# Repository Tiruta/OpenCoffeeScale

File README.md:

# OpenCoffeeScale
an open sourced compact coffee scale.

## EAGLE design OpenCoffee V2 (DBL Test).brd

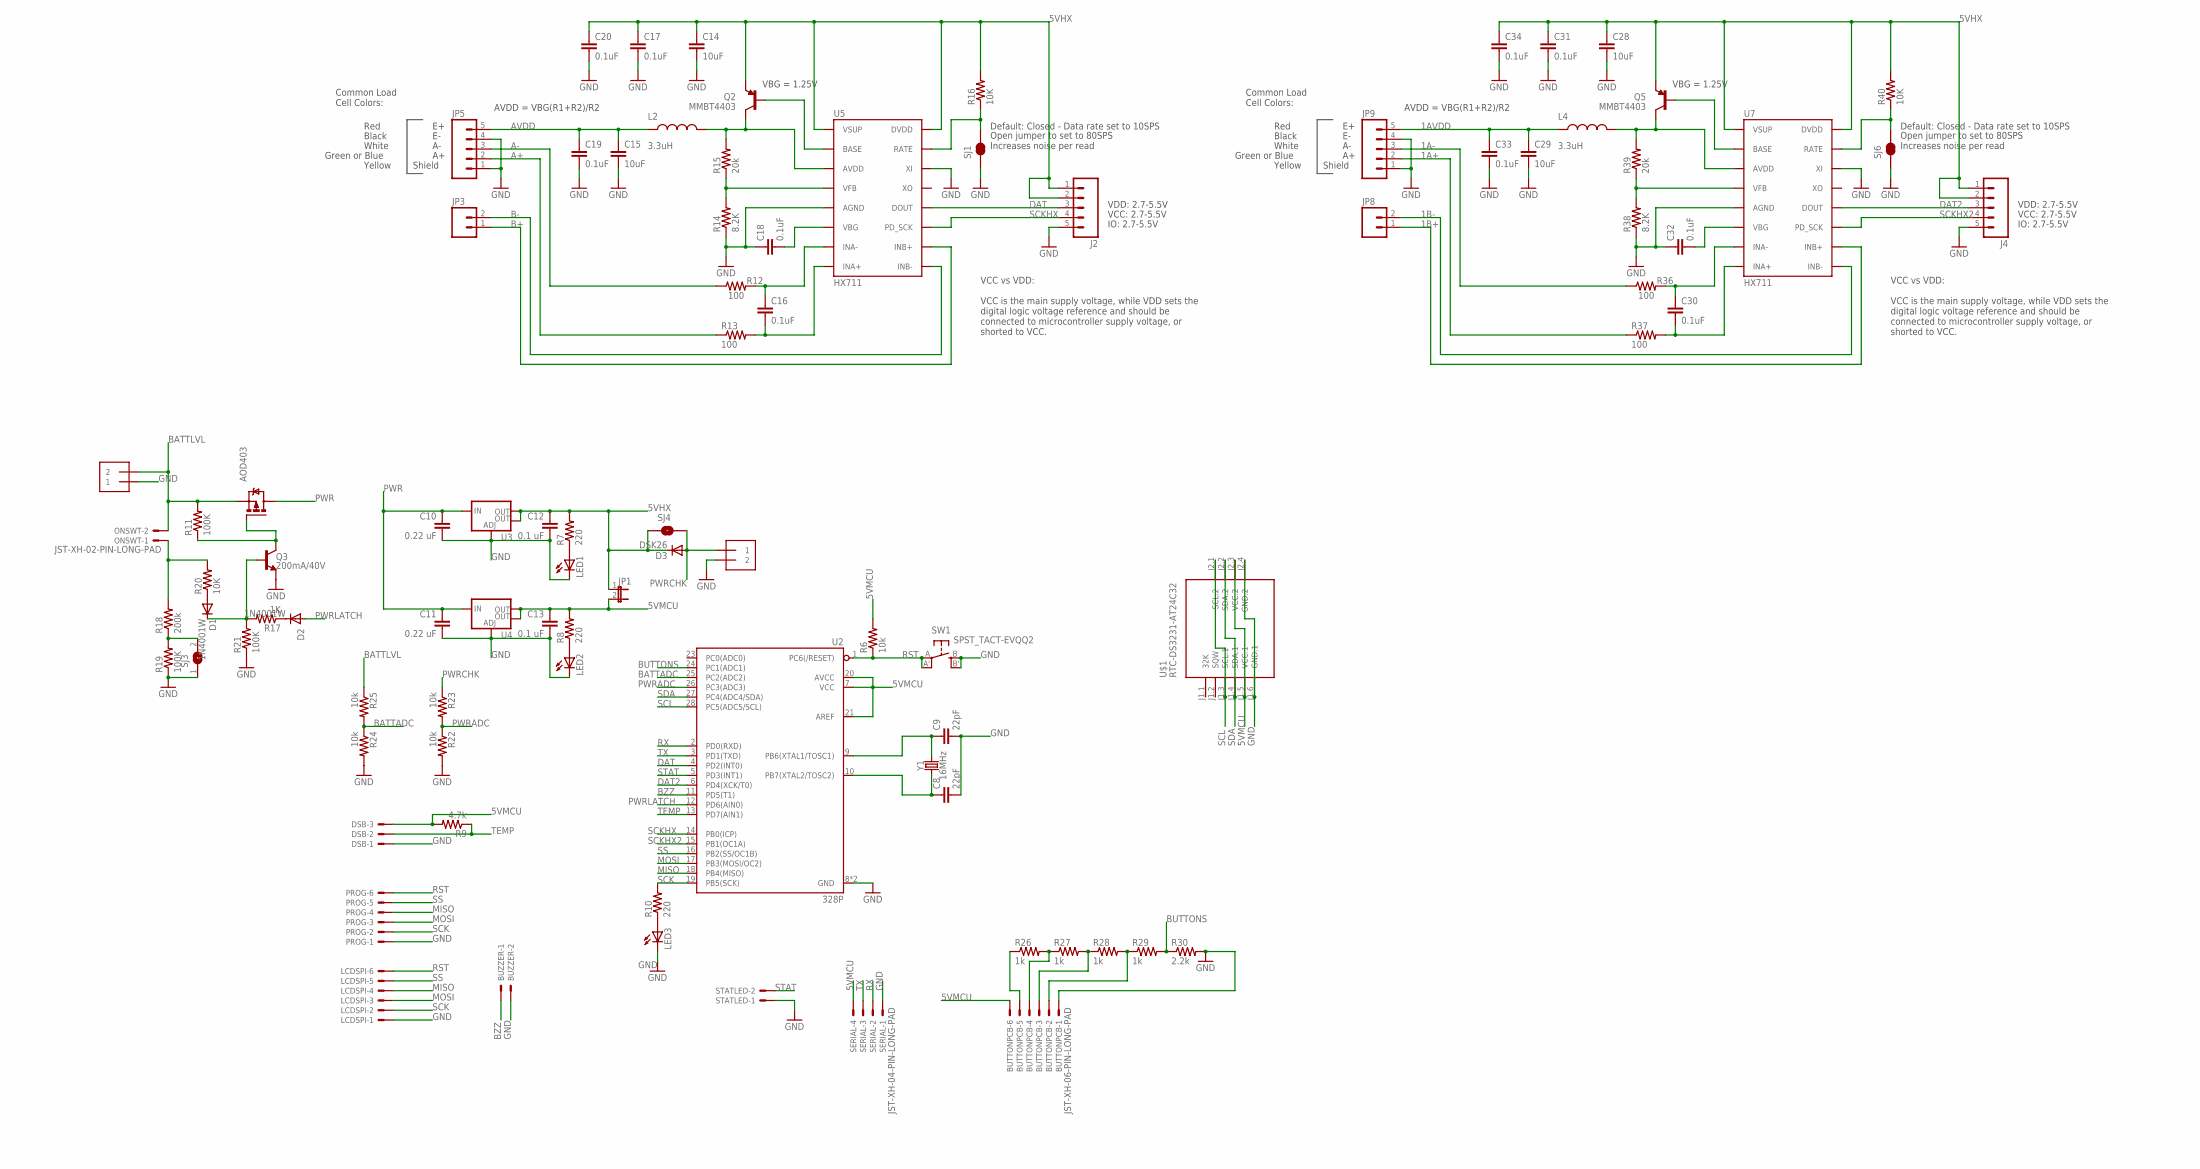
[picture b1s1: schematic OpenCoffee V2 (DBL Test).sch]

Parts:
AOD403: IRFR5305; D-PAK_TO252AA
BATT: 1X2-3.5MM
BUTTONPCB: JST-XH-06-PIN-LONG-PAD; JST-XH-06-PACKAGE-LONG-PAD
BUZZER: JST-XH-02-PIN-LONG-PAD; JST-XH-02-PACKAGE-LONG-PAD
C8, C9: 22pF; C1206
C10, C11: 0.22 uF; C1206
C12, C13: 0.1 uF; C1206
C14, C15, C28, C29: 10uF; 1210
C16, C17, C18, C19, C20, C30, C31, C32, C33, C34: 0.1uF; 0603-CAP
D1, D2: 1N4001W; SOD123
D3: DSK26; SOD123
DSB: JST-XH-03-PIN-LONG-PAD; JST-XH-03-PACKAGE-LONG-PAD
J2, J4: M05PTH; 1X05
JP1: JP1E; JP1
JP3, JP8: M02PTH; 1X02
JP5, JP9: M05PTH; 1X05
L2, L4: 3.3uH; 0805
LCDSPI: JST-XH-06-PIN-LONG-PAD; JST-XH-06-PACKAGE-LONG-PAD
LED1, LED2, LED3: LEDCHIPLED_1206; CHIPLED_1206
ONSWT: JST-XH-02-PIN-LONG-PAD; JST-XH-02-PACKAGE-LONG-PAD
PROG: JST-XH-06-PIN-LONG-PAD; JST-XH-06-PACKAGE-LONG-PAD
Q2, Q5: MMBT4403; SOT23-3
Q3: 200mA/40V; TO-92@1
R6, R22, R23, R24, R25: 10k; R1206
R7, R8, R10: 220; R1206
R9: 4.7k; R1206
R11, R19, R21: 100K; R1206
R12, R13, R36, R37: 100; 0603-RES
R14, R38: 8.2K; 0603-RES
R15, R39: 20k; 0603-RES
R16, R40: 10K; 0603-RES
R17: 1K; R1206
R18: 200k; R1206
R20: 10K; R1206
R26, R27, R28, R29: 1k; R1206
R30: 2.2k; R1206
SERIAL: JST-XH-04-PIN-LONG-PAD; JST-XH-04-PACKAGE-LONG-PAD
SJ1, SJ6: JUMPER-PAD-2-NC_BY_TRACE; PAD-JUMPER-2-NC_BY_TRACE_YES_SILK
SJ3: SJ
SJ4: SOLDERJUMPERNO; SJ_2S-NO
STATLED: JST-XH-02-PIN-LONG-PAD; JST-XH-02-PACKAGE-LONG-PAD
SW1: SPST_TACT-EVQQ2; EVQ-Q2
U2: 328P; DIP28
U3, U4: V_REG_LM1117SOT223; SOT223
U5, U7: HX711; SO16
U$1: RTC-DS3231-AT24C32
USBPWR: 1X2-3.5MM
Y1: 16MHz; HC49US

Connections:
1A+: JP9.2, R37.1
1A-: JP9.3, R36.1
1AVDD: C29.1, C33.1, JP9.5, L4.1
1B+: JP8.1, U7.10 (INB+)
1B-: JP8.2, U7.9 (INB-)
5VHX: C12.1, C14.1, C17.1, C20.1, C28.1, C31.1, C34.1, D3.C, J2.1, J2.2, J4.1, J4.2, JP1.1, Q2.2 (E), Q5.2 (E), R7.2, R16.2, R40.2, SJ4.1, U3.2 (OUT), U3.4 (OUT), U5.1 (VSUP), U5.16 (DVDD), U7.1 (VSUP), U7.16 (DVDD)
5VMCU: BUTTONPCB.6, C13.1, DSB.3, JP1.2, R6.2, R8.2, R9.2, SERIAL.4, U2.7 (VCC), U2.20 (AVCC), U2.21 (AREF), U4.2 (OUT), U4.4 (OUT), U$1.J1.5 (VCC.1), U$1.J2.3 (VCC.2)
A+: JP5.2, R13.1
A-: JP5.3, R12.1
AVDD: C15.1, C19.1, JP5.5, L2.1
B+: JP3.1, U5.10 (INB+)
B-: JP3.2, U5.9 (INB-)
BATTADC: R24.1, R25.2, U2.25 (PC2(ADC2))
BATTLVL: AOD403.3 (S), BATT.2, ONSWT.2, R11.2, R25.1
BUTTONS: R29.2, R30.1, U2.24 (PC1(ADC1))
BZZ: BUZZER.1, U2.11 (PD5(T1))
DAT: J2.3, U2.4 (PD2(INT0)), U5.12 (DOUT)
DAT2: J4.3, U2.6 (PD4(XCK/T0)), U7.12 (DOUT)
GND: BATT.1, BUTTONPCB.1, BUZZER.2, C8.2, C9.2, C10.2, C11.2, C12.2, C13.2, C14.2, C15.2, C17.2, C18.1, C19.2, C20.2, C28.2, C29.2, C31.2, C32.1, C33.2, C34.2, DSB.1, J2.5, J4.5, JP5.1, JP5.4, JP9.1, JP9.4, LCDSPI.1, LED1.C, LED2.C, LED3.C, PROG.1, Q3.1 (E), R14.1, R19.1, R21.1, R22.2, R24.2, R30.2, R38.1, SERIAL.1, SJ1.1, SJ3.1, SJ6.1, STATLED.1, SW1.B (S), SW1.B' (S1), U2.8 (GND), U2.22 (GND), U3.1 (ADJ), U4.1 (ADJ), U5.5 (AGND), U5.14 (XI), U7.5 (AGND), U7.14 (XI), U$1.J1.6 (GND.1), U$1.J2.4 (GND.2), USBPWR.2
MISO: LCDSPI.4, PROG.4, U2.18 (PB4(MISO))
MOSI: LCDSPI.3, PROG.3, U2.17 (PB3(MOSI/OC2))
unnamed: C9.1, U2.9 (PB6(XTAL1/TOSC1)), Y1.2
unnamed: C8.1, U2.10 (PB7(XTAL2/TOSC2)), Y1.1
unnamed: AOD403.1 (G), Q3.3 (C), R11.1
unnamed: Q2.1 (B), U5.2 (BASE)
unnamed: D2.C, R17.1
unnamed: LED1.A, R7.1
unnamed: LED2.A, R8.1
unnamed: R14.2, R15.1, U5.4 (VFB)
unnamed: LED3.A, R10.1
unnamed: C18.2, U5.6 (VBG)
unnamed: L2.2, Q2.3 (C), R15.2, U5.3 (AVDD)
unnamed: R16.1, SJ1.2, U5.15 (RATE)
unnamed: C16.1, R12.2, U5.7 (INA-)
unnamed: C16.2, R13.2, U5.8 (INA+)
unnamed: R18.1, R19.2, SJ3.2
unnamed: D1.A, R20.1
unnamed: D1.C, Q3.2 (B), R17.2, R21.2
unnamed: BUTTONPCB.4, R26.2, R27.1
unnamed: BUTTONPCB.3, R27.2, R28.1
unnamed: BUTTONPCB.2, R28.2, R29.1
unnamed: BUTTONPCB.5, R26.1
unnamed: Q5.1 (B), U7.2 (BASE)
unnamed: R38.2, R39.1, U7.4 (VFB)
unnamed: C32.2, U7.6 (VBG)
unnamed: L4.2, Q5.3 (C), R39.2, U7.3 (AVDD)
unnamed: R40.1, SJ6.2, U7.15 (RATE)
unnamed: C30.1, R36.2, U7.7 (INA-)
unnamed: C30.2, R37.2, U7.8 (INA+)
ONSWT: ONSWT.1, R18.2, R20.2
PWR: AOD403.4 (D), C10.1, C11.1, U3.3 (IN), U4.3 (IN)
PWRADC: R22.1, R23.2, U2.26 (PC3(ADC3))
PWRCHK: D3.A, R23.1, SJ4.2, USBPWR.1
PWRLATCH: D2.A, U2.12 (PD6(AIN0))
RST: LCDSPI.6, PROG.6, R6.1, SW1.A, SW1.A' (P1), U2.1 (PC6(/RESET))
RX: SERIAL.2, U2.2 (PD0(RXD))
SCK: LCDSPI.2, PROG.2, R10.2, U2.19 (PB5(SCK))
SCKHX: J2.4, U2.14 (PB0(ICP)), U5.11 (PD_SCK)
SCKHX2: J4.4, U2.15 (PB1(OC1A)), U7.11 (PD_SCK)
SCL: U2.28 (PC5(ADC5/SCL)), U$1.J1.3 (SCL.1), U$1.J2.1 (SCL.2)
SDA: U2.27 (PC4(ADC4/SDA)), U$1.J1.4 (SDA.1), U$1.J2.2 (SDA.2)
SS: LCDSPI.5, PROG.5, U2.16 (PB2(SS/OC1B))
STAT: STATLED.2, U2.5 (PD3(INT1))
TEMP: DSB.2, R9.1, U2.13 (PD7(AIN1))
TX: SERIAL.3, U2.3 (PD1(TXD))

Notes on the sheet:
VCC: 2.7-5.5V
VBG = 1.25V
AVDD = VBG(R1+R2)/R2
Default: Closed - Data rate set to 10SPS
Open jumper to set to 80SPS Increases noise per read
Red
Black
White
Green or Blue
Common Load Cell Colors:
IO: 2.7-5.5V
Shield
Yellow
VDD: 2.7-5.5V
VCC vs VDD: VCC is the main supply voltage, while VDD sets the digital logic voltage reference and should be connected to microcontroller supply voltage, or shorted to VCC.

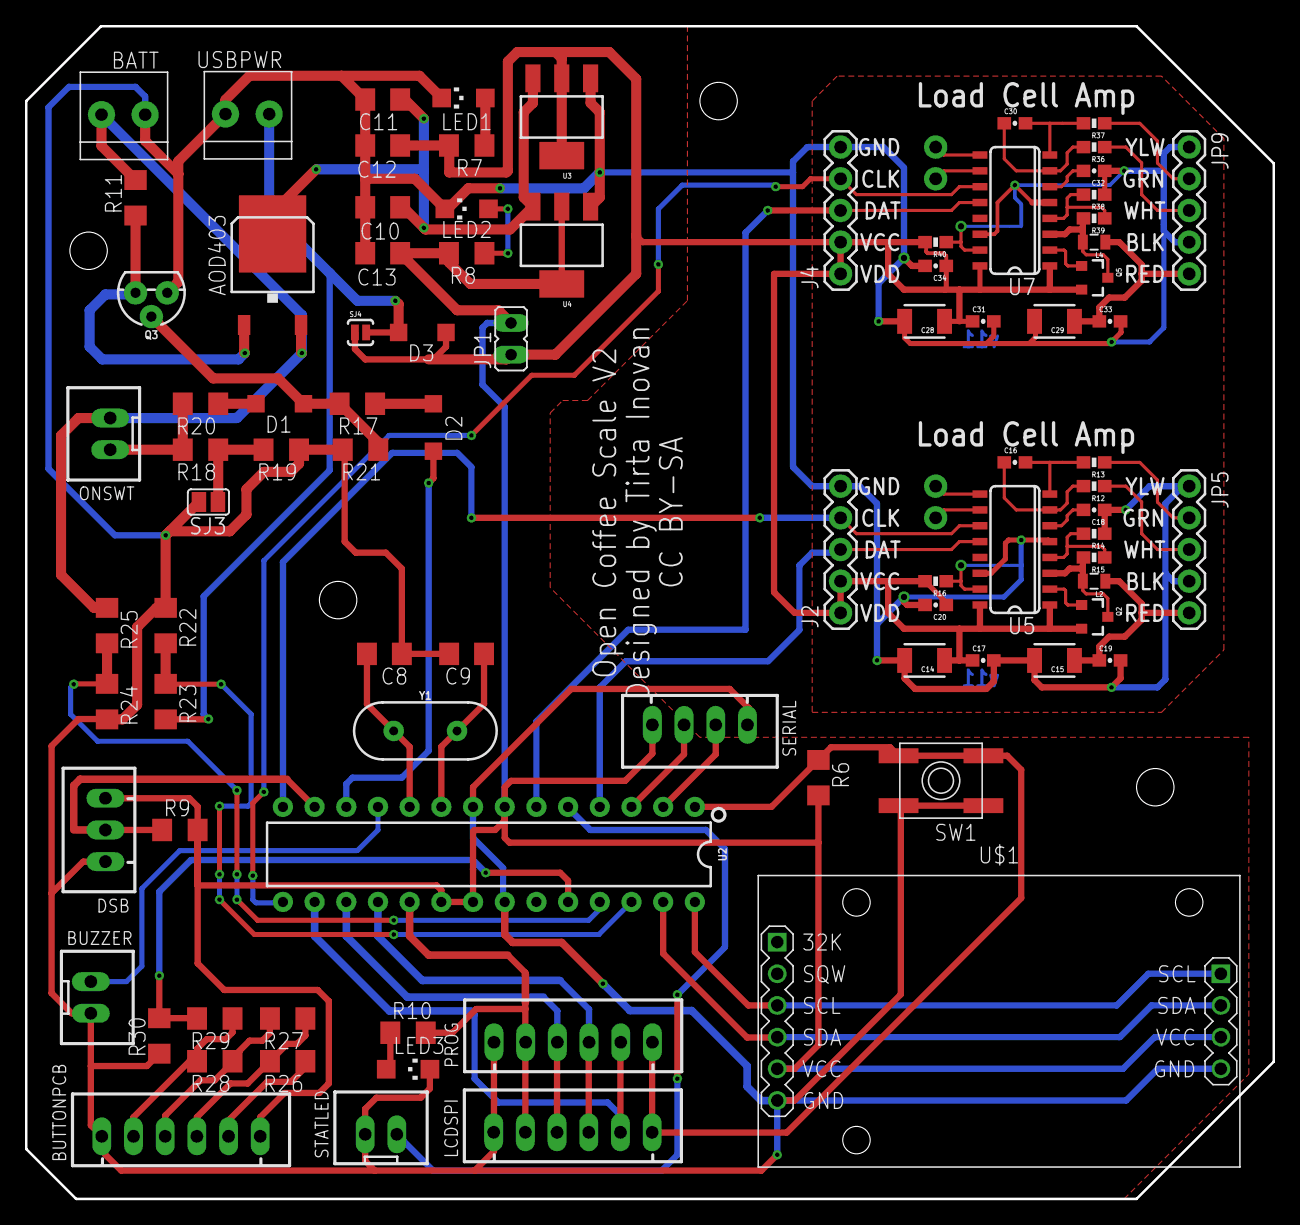
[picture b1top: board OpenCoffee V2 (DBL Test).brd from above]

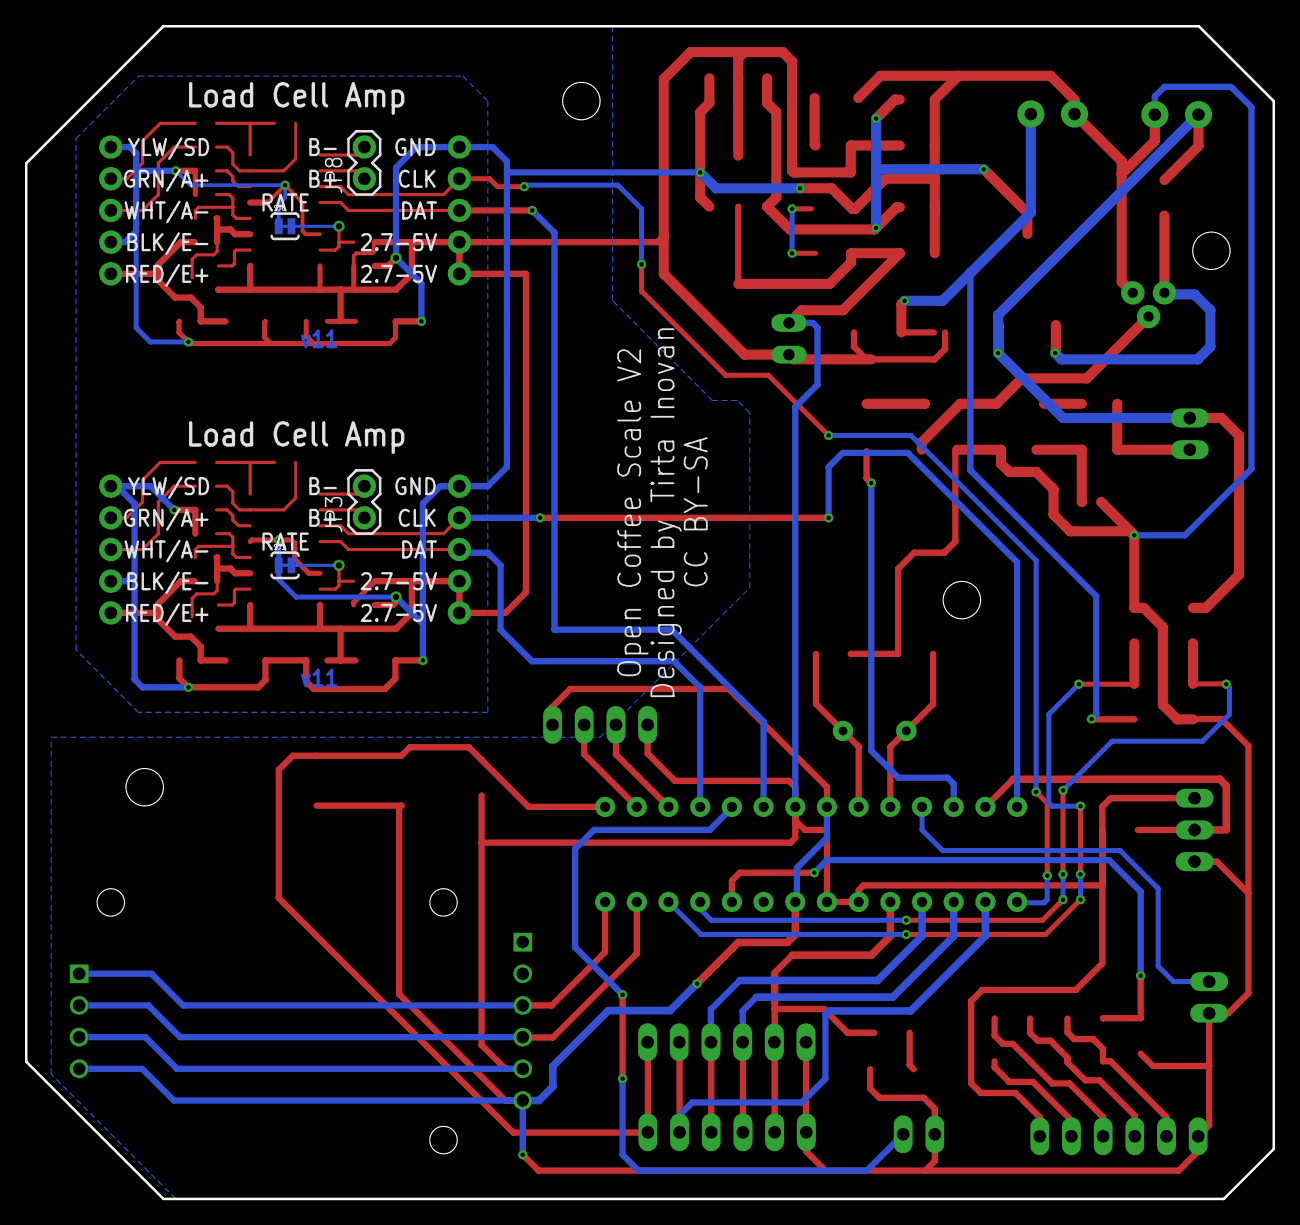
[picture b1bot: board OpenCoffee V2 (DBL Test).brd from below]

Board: 2 copper layers, 100.0 x 94.0 mm, 91 parts (4 on the bottom side), 65 nets.

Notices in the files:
OpenCoffee V2 (DBL Test).brd:
CC BY-SA
parts and their libraries:
SparkFun-DiscreteSemi: Licensing: Creative Commons ShareAlike 4.0 International - https://creativecommons.org/licenses/by-sa/4.0
diy-modules: Released under the Creative Commons Attribution 4.0 International License: http://creativecommons.org/licenses/by/4.0
